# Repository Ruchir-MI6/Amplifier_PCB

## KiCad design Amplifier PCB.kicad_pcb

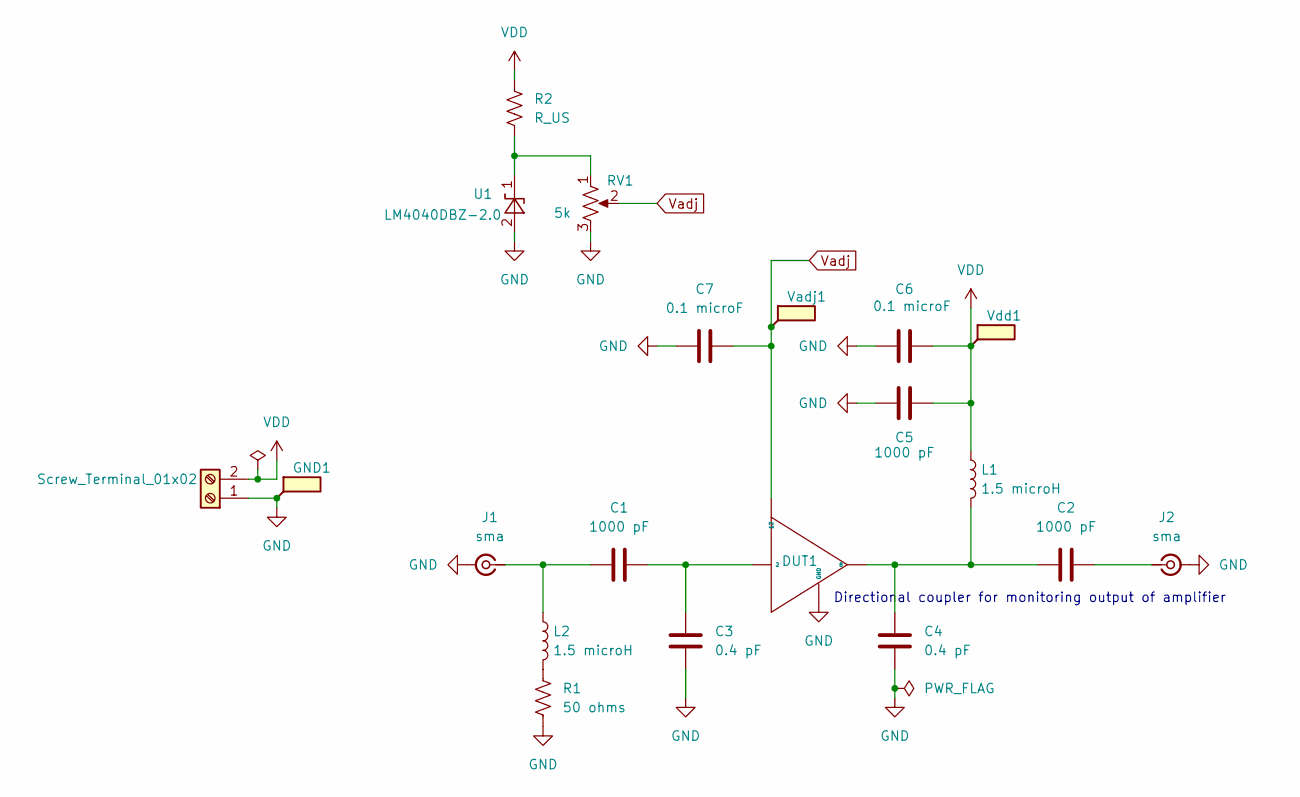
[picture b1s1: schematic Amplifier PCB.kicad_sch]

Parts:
C1, C2, C5: 1000 pF; C_0402_1005Metric; PARTNO GRM1555C1H102JA01D; DIGIKEY 490-3244-1-ND
C3, C4: 0.4 pF; C_0402_1005Metric; PARTNO GJM1555C1HR40WB01D; DIGIKEY 490-11249-1-ND
C6, C7: 0.1 microF; C_0402_1005Metric; PARTNO GRM155R71H104KE14J; DIGIKEY 490-13342-1-ND
DUT1: Chip; PARTNO PMA3-43-1W+
GND1: TestPoint_Flag; TestPoint_Pad_D2.5mm
J1, J2: sma; SMA_Samtec_SMA-J-P-H-ST-EM1_EdgeMount
J3: Screw_Terminal_01x02; TerminalBlock_Phoenix_PT-1,5-2-3.5-H_1x02_P3.50mm_Horizontal
L1, L2: 1.5 microH; L_Coilcraft_0805LS-152XJEC; PARTNO 0805LS-152XJRC; Mouser 994-0805LS-152XJRC
R1: 50 ohms; R_0402_1005Metric; PARTNO RN73R1ETTP50R0F50; DIGIKEY 2019-RN73R1ETTP50R0F50CT-ND
R2: R_US; R_0805_2012Metric; PARTNO RNCP0805FTD15K0; DIGIKEY RNCP0805FTD15K0CT-ND
RV1: 5k; Potentiometer_Bourns_3314R-1_Vertical_Hole; PARTNO 3314R-1-502E; Mouser 652-3314R-1-502E
U1: LM4040DBZ-2.0; SOT-23; PARTNO LM4040D20IDBZR; DIGIKEY 296-20899-1-ND
Vadj1: TestPoint_Flag; TestPoint_Pad_D2.5mm
Vdd1: TestPoint_Flag; TestPoint_Pad_D2.5mm

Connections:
GND: C3.2, C4.2, C5.1, C6.1, C7.1, DUT1.GND, GND1.1, J1.2 (Ext), J2.2 (Ext), J3.1, R1.2, RV1.3, U1.2 (A)
unnamed: C1.2, C3.1, DUT1.2
unnamed: C2.1, C4.1, DUT1.8, L1.2
unnamed: C1.1, J1.1 (In), L2.1
unnamed: C2.2, J2.1 (In)
unnamed: L2.2, R1.1
unnamed: R2.2, RV1.1, U1.1 (K)
VDD: C5.2, C6.2, J3.2, L1.1, R2.1, Vdd1.1
Vadj: C7.2, DUT1.12, RV1.2, Vadj1.1

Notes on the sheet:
Directional coupler for monitoring output of amplifier

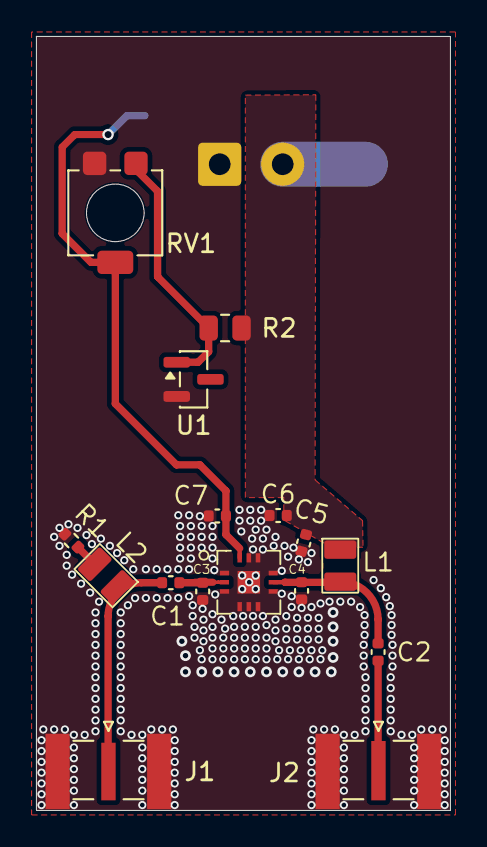
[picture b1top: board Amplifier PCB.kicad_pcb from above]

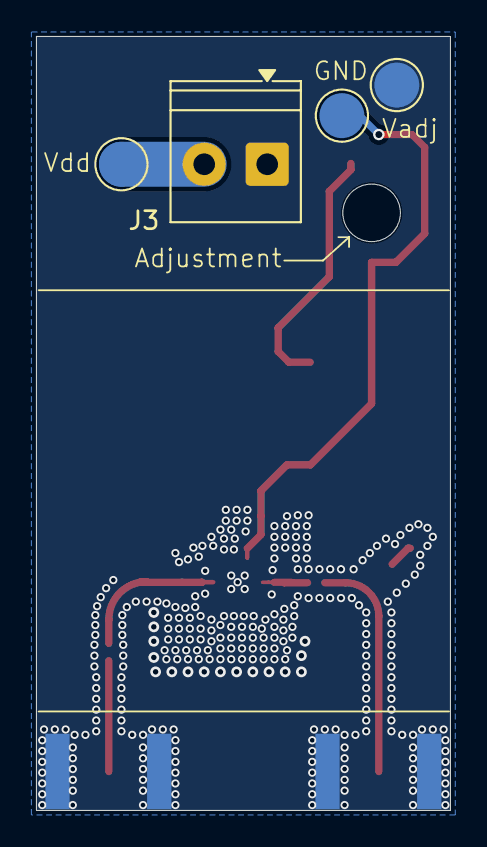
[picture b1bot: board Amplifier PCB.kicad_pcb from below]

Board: 4 copper layers, 23.0 x 43.0 mm, 20 parts (4 on the bottom side), 9 nets.

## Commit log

2026-05-13 Initial commit of Amplifier PCB KiCad
2026-05-13 Update not really
2026-05-17 Final update
